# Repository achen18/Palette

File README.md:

# Palette
8 key macropad with a rotary encoder and OLED display. It features 8 SK6812 LEDs for a backlight effect and runs on KMK firmware.  

## PCB  
Designed using Kicad.  

Schematic  

PCB  

## Case  
3d printed case desinged using Fusion 360. Multiple parts designed for ease of assembly and printing with minimal supports.  

## Firmware  
Macropad runs on KMK software.  
- Rotary encoder changes volume. Press to play/pause.
- 8 keys can be changed through KMK.
- Multiple layers for different day-to-day needs. Cycle between layers with a custom key!
- Custom OLED-dispalyed images to indicate current layer (working on images, using text as placeholder for now).

## Bill of Materials  
- 1 x Seeed XIAO RP2040
- 9 x Through-hole 1N4148 Diodes
- 8 x MX-Style switches
- 1 x EC11 Rotary encoder
- 1 x 0.91 inch OLED display
- 8 x Blank DSA keycaps
- 8 x SK6812 MINI-E LEDs
- 4 x M3x16mm screws
- 4 x M3x5mx4mm heatset inserts
- 1 x Case (4 3D printed parts)

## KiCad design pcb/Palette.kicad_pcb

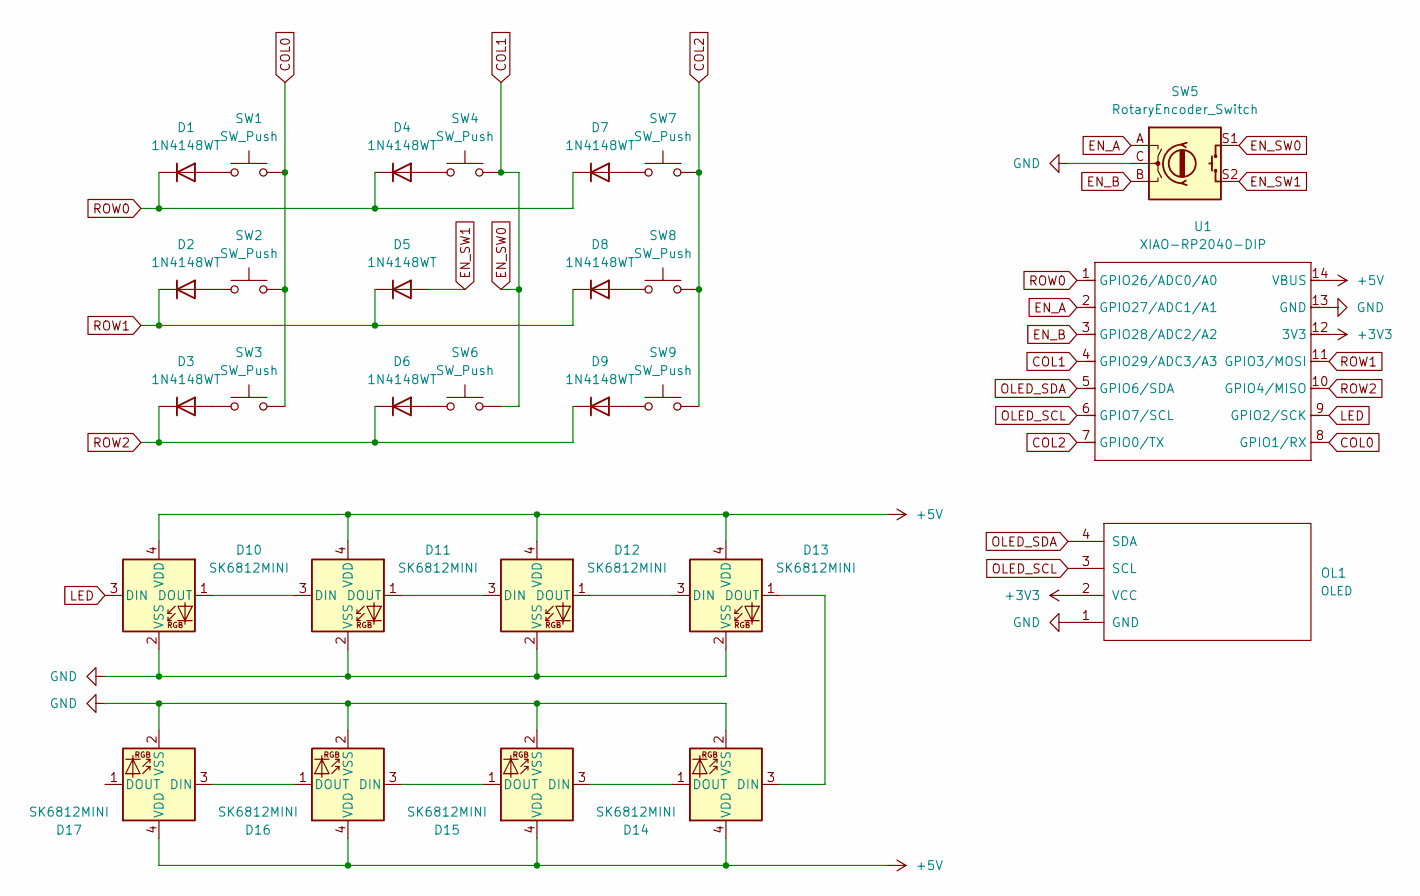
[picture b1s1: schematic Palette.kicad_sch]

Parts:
D1, D2, D3, D4, D5, D6, D7, D8, D9: 1N4148WT; D_DO-35_SOD27_P7.62mm_Horizontal
D10, D11, D12, D13, D14, D15, D16, D17: SK6812MINI; LED_SK6812MINI_PLCC4_3.5x3.5mm_P1.75mm
OL1: OLED; SSD1306-0.91-OLED-4pin-128x32
SW1, SW2, SW3, SW4, SW6, SW7, SW8, SW9: SW_Push; SW_Cherry_MX_1.00u_PCB
SW5: RotaryEncoder_Switch; RotaryEncoder_Alps_EC11E-Switch_Vertical_H20mm
U1: XIAO-RP2040-DIP

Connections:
+3V3: OL1.2 (VCC), U1.12 (3V3)
+5V: D10.4 (VDD), D11.4 (VDD), D12.4 (VDD), D13.4 (VDD), D14.4 (VDD), D15.4 (VDD), D16.4 (VDD), D17.4 (VDD), U1.14 (VBUS)
COL0: SW1.2, SW2.2, SW3.2, U1.8 (GPIO1/RX)
COL1: SW4.2, SW5.S1, SW6.2, U1.4 (GPIO29/ADC3/A3)
COL2: SW7.2, SW8.2, SW9.2, U1.7 (GPIO0/TX)
EN_A: SW5.A, U1.2 (GPIO27/ADC1/A1)
EN_B: SW5.B, U1.3 (GPIO28/ADC2/A2)
EN_SW1: D5.2 (A), SW5.S2
GND: D10.2 (VSS), D11.2 (VSS), D12.2 (VSS), D13.2 (VSS), D14.2 (VSS), D15.2 (VSS), D16.2 (VSS), D17.2 (VSS), OL1.1 (GND), SW5.C, U1.13 (GND)
LED: D10.3 (DIN), U1.9 (GPIO2/SCK)
unnamed: D1.2 (A), SW1.1
unnamed: D2.2 (A), SW2.1
unnamed: D3.2 (A), SW3.1
unnamed: D4.2 (A), SW4.1
unnamed: D6.2 (A), SW6.1
unnamed: D7.2 (A), SW7.1
unnamed: D8.2 (A), SW8.1
unnamed: D9.2 (A), SW9.1
unnamed: D10.1 (DOUT), D11.3 (DIN)
unnamed: D11.1 (DOUT), D12.3 (DIN)
unnamed: D12.1 (DOUT), D13.3 (DIN)
unnamed: D13.1 (DOUT), D14.3 (DIN)
unnamed: D14.1 (DOUT), D15.3 (DIN)
unnamed: D15.1 (DOUT), D16.3 (DIN)
unnamed: D16.1 (DOUT), D17.3 (DIN)
OLED_SCL: OL1.3 (SCL), U1.6 (GPIO7/SCL)
OLED_SDA: OL1.4 (SDA), U1.5 (GPIO6/SDA)
ROW0: D1.1 (K), D4.1 (K), D7.1 (K), U1.1 (GPIO26/ADC0/A0)
ROW1: D2.1 (K), D5.1 (K), D8.1 (K), U1.11 (GPIO3/MOSI)
ROW2: D3.1 (K), D6.1 (K), D9.1 (K), U1.10 (GPIO4/MISO)

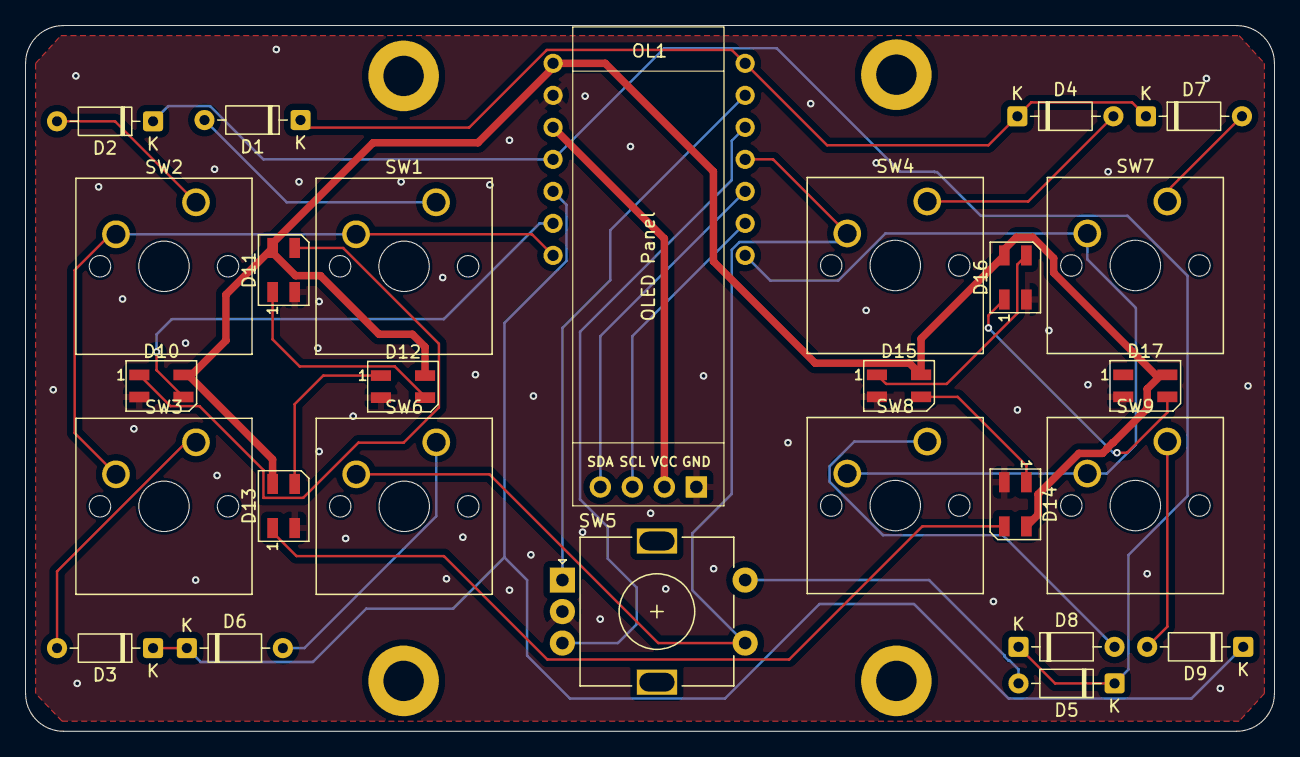
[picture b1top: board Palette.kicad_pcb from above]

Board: 2 copper layers, 99.1 x 56.0 mm, 28 parts (1 on the bottom side), 30 nets.

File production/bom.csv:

Designator,Footprint,Quantity,Value,LCSC Part #
"_3, _2, ",,3,,
"D1, D2, D3, D4, D5, D6, D7, D8, D9",D_DO-35_SOD27_P7.62mm_Horizontal,9,1N4148WT,
"D10, D11, D12, D13, D14, D15, D16, D17",LED_SK6812MINI_PLCC4_3.5x3.5mm_P1.75mm,8,SK6812MINI,
OL1,SSD1306-0.91-OLED-4pin-128x32,1,OLED,
"SW1, SW2, SW3, SW4, SW6, SW7, SW8, SW9",SW_Cherry_MX_1.00u_PCB,8,SW_Push,
SW5,RotaryEncoder_Alps_EC11E-Switch_Vertical_H20mm,1,RotaryEncoder_Switch,
U1,XIAO-RP2040-DIP,1,XIAO-RP2040-DIP,

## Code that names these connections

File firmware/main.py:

import board
import busio

from kmk.kmk_keyboard import KMKKeyboard
from kmk.keys import KC
from kmk.keys import Key
from kmk.scanners import DiodeOrientation

from kmk.modules.encoder import EncoderHandler
from kmk.extensions.media_keys import MediaKeys

from kmk.modules.layers import Layers

from kmk.extensions.RGB import RGB

from kmk.extensions.display import Display, TextEntry, ImageEntry


# inititalize keyboard isntance
keyboard = KMKKeyboard()

encoder_handler = EncoderHandler
keyboard.modules.append(encoder_handler)

keyboard.extensions.append(MediaKeys())

class RGBChange(RGB):
    def on_layer_change(self, layer):
        if layer == 0:
            self.set_hsv_fill(0, self.sat_default, self.val_default)   # red
        elif layer == 1:
            self.set_hsv_fill(170, self.sat_default, self.val_default) # blue
        elif layer == 2:
            self.set_hsv_fill(43, self.sat_default, self.val_default) # yelloe

        # update LEDs manually 
        self.show()

rgb = RGBChange(
    pixel_pin = board.GP9,
    num_pixels = 8,
    val_limit = 100,
    rgb_order = (1, 0, 2),
    hue_default = 0, 
    sat_default = 255,
    val_default = 100,
)

keyboard.extensions.append(rgb)

# old code
# class RGBLayers(Layers):
#     def activate_layer(self, keyboard, layer, idx=None):
#         super().activate_layer(keyboard, layer, idx)
#         rgb.on_layer_change(layer)

#     # def deactivate_layer(self, keyboard, layer):
#     #     super().deactivate_layer(keyboard, layer)
#     #     rgb.on_layer_change(keyboard.active_layers[0])

# keyboard.modules.append(RGBLayers())

# define which pins on XIAO the encoder uses
encoder_handler.pins = (
    (board.GP17, board.GP15, None,)
)

# defining the encoder functions (same across all layers)
# the button is not defined because it is wired into the key matrix
encoder_handler.map = [ 
    ((KC.AUDIO_VOL_UP, KC.AUDIO_VOL_DOWN, ),), # layer 0
    ((KC.AUDIO_VOL_UP, KC.AUDIO_VOL_DOWN, ),), # layer 1
    ((KC.AUDIO_VOL_UP, KC.AUDIO_VOL_DOWN, ),), # layer 2
]

# defining what pins matrix columns and rows correspond to and putting them in the like cols and rows
COL0 = board.GP8
COL1 = board.GP4
COL2 = board.GP7
ROW0 = board.GP1
ROW1 = board.GP11
ROW2 = board.GP10

# putting them more in the columns and rows
keyboard.col_pins = (COL0, COL1, COL2)
keyboard.row_pins = (ROW0, ROW1, ROW2)
keyboard.diode_orientation = DiodeOrientation.COL2ROW
# tell it that the diodes are like pointing from columns 2 ("to") rows

# old code for custom key layer cycle
# LAYER_COUNT = 3
# def cycle_layer(keyboard, key):
#     current = keyboard.active_layers[0]
#     next = (current + 1) % LAYER_COUNT

#     keyboard.active_layers = [next]
#     rgb.on_layer_change(next)

#     return False

# new code that creates custom key derived from Key base class
class CycleKey(Key):

    # when defining, pass in the layer count DONT FORGET WHEN CHANGING YOU
    def __init__(self, layer_count):
        super().__init__()
        self.layer_count = layer_count

    # on press, find the next layer, if at end, cycle back to 0, set next as active, call rgb layer change
    def on_press(self, keyboard, coord_int=None):
        current = keyboard.active_layers[0]
        next_layer = (current + 1) % self.layer_count
        keyboard.active_layers = [next_layer]
        rgb.on_layer_change(next_layer) 

KC_CYCLE = CycleKey(3)

# encoder button wired in key matrix
# layer switch button puts the next layer on the top for a cycling effect (hopefully)

# assign actual keys later
keyboard.keymap = [
    # layer 0 - regular?
    [[KC.A,  KC.A,   KC_CYCLE],
    [KC.A,  KC.MEDIA_PLAY_PAUSE,   KC.A],
    [KC.A,  KC.A,   KC.A],],
    
    # layer 1 - gaming
    [[KC.A,  KC.A,   KC_CYCLE],
    [KC.A,  KC.MEDIA_PLAY_PAUSE,   KC.A],
    [KC.A,  KC.A,   KC.A],],

    # layer 2 - art
    [[KC.A,  KC.A,   KC_CYCLE],
    [KC.A,  KC.MEDIA_PLAY_PAUSE,   KC.A],
    [KC.A,  KC.A,   KC.A],],
]

from kmk.extensions.display.ssd1306 import SSD1306

bus = busio.I2C(board.GP6, board.GP5)

driver = SSD1306(
    i2c=bus,
    device_address=0x3C,
)

display = Display(
    display=driver,
    width=128,
    height=32,
    brightness = 0.8,
)

# make and change these to images later
display.entries = [
    TextEntry(text = "1", x = 0, y = 0, layer = 0),
    TextEntry(text = "2", x = 0, y = 0, layer = 1),
    TextEntry(text = "3", x = 0, y = 0, layer = 2),
]

keyboard.extensions.append(display)

if __name__ == '__main__':
    keyboard.go()

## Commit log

2025-07-23 upload Palette project files
